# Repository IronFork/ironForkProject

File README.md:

# ironForkProject
 robotic arm helping people with disabilities to eat
 
 https://ironfork.fr

READ ME

I - INTRODUCTION

  a) Présentation
  
  b) Objectifs du projet
  
II - MONTER LE ROBOT

  a) Imprimer les pièces en 3D
  
  b) Se procurer les moteurs
  
  c) Se procurer les composants annexes 
  
III - FAIRE FONCTIONNER LE ROBOT

IV - EXPLICATION DU CODE SOURCE

  a) La partie mécanique 
  
  b) La partie programmation
  
V - PISTES D'AMÉLIORATION

I - INTRODUCTION 

a) Présentation : 
Projet mené par un groupe de 12 étudiants en partenariat avec l'IEM "Christian Dabbadie" dans le cadre de leurs études à Centrale Lille. 

b) Objectifs du projet : 
Concevoir un bras robotique permettant aux personnes en situation de handicap d'avoir une plus grande autonomie lors de leurs repas. 
Projet en open source avec une licence GPL. 
L'un des objectifs du projet est de rendre le bras imprimable en 3D facilement dans un fablab.

I - MONTER LE ROBOT 

Vous aurez besoin d'une imprimante 3D et de ... bobines de PLA. Le reste des composants à commander est indiqué dans les étapes suivantes. Le budget estimé est de 500€ environs. 

a) Imprimer les pièces en 3D : 
Ouvrir le dossier fichiers_stl. Ce dossier contient les fichiers STL de chaque pièce du robot, organisées en sous-ensembles. Un sous-dossier nommé "assemblages" contient les fichiers STL des différents sous-ensembles, et de l'assemblage complet. 

Liste des pièces à imprimer en 3D : 

Pour le socle : 
  - 3 sous-socles différents (c'est le plancher du robot, les 3 sous-socles sont sur le même ficher STL)
  - 1 bol
  - 1 socle (en forme de petite tablette)
  - 1 adaptateur socle-moteur (permet de fixer le moteur sous le socle)
  - 1 poulie socle (poulie fixée sur l'axe moteur)
  
Pour la Tourelle : 
  - 1 Tourelle (placée en liaison pivot avec le socle, elle soutient le bras)
  - 1 poulie tourelle ( poulie fixée dans l'axe de la tourelle et reliée à la poulie socle par une courroie)
  - 2 adaptateurs tourelle-moteurs (permettent de fixer 2 moteurs sur la tourelle)
  
Pour le bras : 
  - 1 bras Tourelle (c'est le bras relié à la tourelle en pivot)
  - 1 adaptateur bras-moteur (permet de fixer le moteur sur le bras)
  
Pour l'avant-bras : 
  - 1 avant-bras (ressemble au bras-tourelle mais est légèrement différent)
  - 1 adaptateur avant-bras-moteur (permet de fixer le moteur)
  
Pour la pince : 
  - 1 pince 

Pour l'assemblage, référez-vous aux fichiers STL représentant les sous-ensembles du robot. 

b) Se procurer les moteurs : 
Vous aurez besoin de cinq moteurs dynamixel XL430-W250-T.
documentation technique sur github : https://github.com/ROBOTIS-GIT/emanual/blob/master/docs/en/dxl/x/xl430-w250.md

c) Se procurer les composants annexes : 
voir notice. (visserie, fils électriques, rasberry pi, carte de programmation, etc... )

d) Assembler le robot : 
Vous devez vous référer au dossier fichiers_stl pour voir le rôle de chaque composant au sein de l'assemblage complet. 
Référez-vous également au schéma électrique pour les différents branchements. 
Référez-vous à la notice pour vous aider

L'assemblage du robot est maintenant terminé. 

II - FAIRE FONCTIONNER LE ROBOT  

[à compléter, en attendant, cf notice.]

III - EXPLICATION DU CODE SOURCE 

a) La partie mécanique

Le schéma cinématique : 
Nous avons choisi un nombre de 5 pièces d'un point de vue cinématique. Elles sont reliées en série au bâti par cinq liaisons pivot. Une pivot verticale lie le BATI avec la TOURELLE, une pivot horizontale lie la TOURELLE au BRAS, une pivot horizontale lie le BRAS à l'AVANT-BRAS, et une liaison pivot horizontale lie l'AVANT-BRAS à la PINCE. 
Ce choix de 4 pièces et de cinq liaisons pivot nous permet de positionner la PINCE à n'importe quel endroit dans l'espace, et de réaliser un maximum de mouvements en gardant la PINCE à l'horizontal (ce qui permet de déplacer une cuillère sans renverser son contenu). Ce choix de cinématique permet des mouvements fluides et précis. Référez-vous au fichier STL de l'assemblage complet pour vous représenter l'architecture du robot. 

La tourelle : 
La tourelle est au bâti par une liason pivot verticale. Cette liaison permet au robot de tourner sur lui même et de déplacer la cuillère de manière grossière latéralement de gauche à droite. 
Cette liasion qui est la première est la seule à supporter toute la structure du robot, et subit donc beaucoup d'efforts. Il y a également beaucoup de forttements, de par l'appui de la tourelle sur le bâti. Nous avons choisi d'utiliser un coussinet à collerette entre le bati et la tourelle pour minimiser les frottements. La liasion est motorisée par un servomoteur Dynamixel positionné à quelques centimètres de la liaison, et relié par une liaison poulie-couroie. Cela permet de résoudre le problème de coaxialité du moteur avec la liasion, et d'écentuels efforts supportés par l'axe du moteur.

La tourelle et le bras : 
La tourelle et le bras sont reliés par une liaison pivot horizontale. Cette liaison contribue grandement au mouvement d'avant en arrière de la cuillère. 
Encore une fois, cette liasion supporte une bonne partie de la structure du robot, surtout quand celui-ci est étendu. Dans ce cas là, le couple dans l'axe de la liaison est particulièrement élevé. C'est pourquoi nous avons choisi de placer non pas un, mais deux servomoteurs Dynamixel en parallèle de manière à pouvoir axionner cette liasion avec une puissance suffisante. Deux adaptateurs sont vissés au bâti avec des vis à bois permettent de fixer les servomoteurs. 

Le bras et l'avant-bras : 
Le bras est relié à l'avant-bras par une liasion pivot motorisée par un servomoteur Dynamixel. Cette laison contribue grandement au mouvement vertical de bas en haut de la cuillère. Un adaptateur vissé au bras par des vis à bois permet de fixer le moteur. 

L'avant-bras et la pince : 
L'avant-bras et la pince sont reliés entre eux par une liaison pivot motorisée par un servomoteur Dynamixel. Cette liaison permet d'effectuer un mouvement vertical de précison, à la manière d'un poignet. Un adaptateur vissé à l'avant-bras permet de fixer le moteur. 

La pince : 
La pince présente une fente ainsi qu'un trou. Ce trou permet d'y placer un insert de filletage, et la fente permet d'y glisser un manche de cuillère. Ainsi, avec une vis de pression, la cuillère peut être bloquée dans la fente. L'avantage de ce système est qu'il permet l'utilisation d'une cuillère quelconque. 

Le bol : 
Un bol imprimé en 3D est fixé sur le support. ce bol a une forme particulière qui permet à la nourriture d'être centrée dans la zone de pelletage. De plus, le rebord avancé peu haut et le rebord éloigné élevé permettent une introduction de la cuillère aisée, et un raclage facilité. L'avantage de ce système est qu'il permet de n'avoir qu'un seul et unique geste de peletage pour le robot. L'inconvénient est le côté sanitaire : il faut imprimer le bol en PET, et les stries de l'impression 3D peuvent occasionner des copeaux de plastiques dans la nourriture lors du raclage. 

b) La partie programmation

Le choix des composants

La trajectoire choisie 

Explication des fichiers 

IV - PISTES D'AMELIORATION

- sécurité, détection d'erreur informatique
- tests en conditions réeelles (personne en situation de handicap)
- améliorer le système de fixation de la cuillère 
- réduire le volume
- trouver des composants moins cher
- reconnaissance faciale
- ...

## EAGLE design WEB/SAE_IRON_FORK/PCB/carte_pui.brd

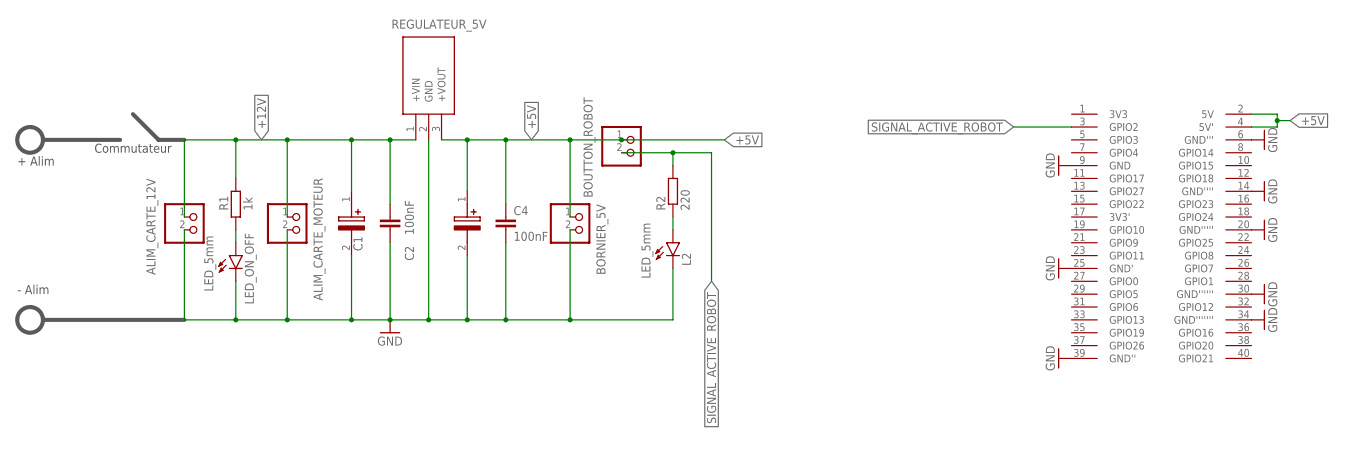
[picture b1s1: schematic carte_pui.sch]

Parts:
ALIM_CARTE_12V: BORNIER_2_ROND_LARGE
ALIM_CARTE_MOTEUR: BORNIER_2_ROND_LARGE
BORNIER_5V: BORNIER_2_ROND_LARGE
BOUTTON_ROBOT: BORNIER_2_ROND_LARGE
C1, C3: 10uF; CAPPRD350W65D800H1300
C2, C4: 100nF; C050-030X040
L2: LED_5mm; LED5MM
LED_ON_OFF: LED_5mm; LED5MM
R1: 1k; 0207/7-90
R2: 220; 0207/7-90
REGULATEUR_5V: TSR_2-2450; TSR-2
U$1: PI4

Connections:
+5V: BORNIER_5V.1, BOUTTON_ROBOT.1, C3.1 (+), C4.1, REGULATEUR_5V.3 (+VOUT), U$1.2 (5V), U$1.4 (5V')
+12V: ALIM_CARTE_12V.1, ALIM_CARTE_MOTEUR.1, C1.1 (+), C2.1, R1.2, REGULATEUR_5V.1 (+VIN)
GND: ALIM_CARTE_12V.2, ALIM_CARTE_MOTEUR.2, BORNIER_5V.2, C1.2 (-), C2.2, C3.2 (-), C4.2, L2.K (C), LED_ON_OFF.K (C), REGULATEUR_5V.2 (GND), U$1.6 (GND'''), U$1.9 (GND), U$1.14 (GND''''), U$1.20 (GND'''''), U$1.25 (GND'), U$1.30 (GND''''''), U$1.34 (GND'''''''), U$1.39 (GND'')
unnamed: LED_ON_OFF.A, R1.1
unnamed: L2.A, R2.1
SIGNAL_ACTIVE_ROBOT: BOUTTON_ROBOT.2, R2.2, U$1.3 (GPIO2)

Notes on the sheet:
Commutateur
+ Alim
- Alim

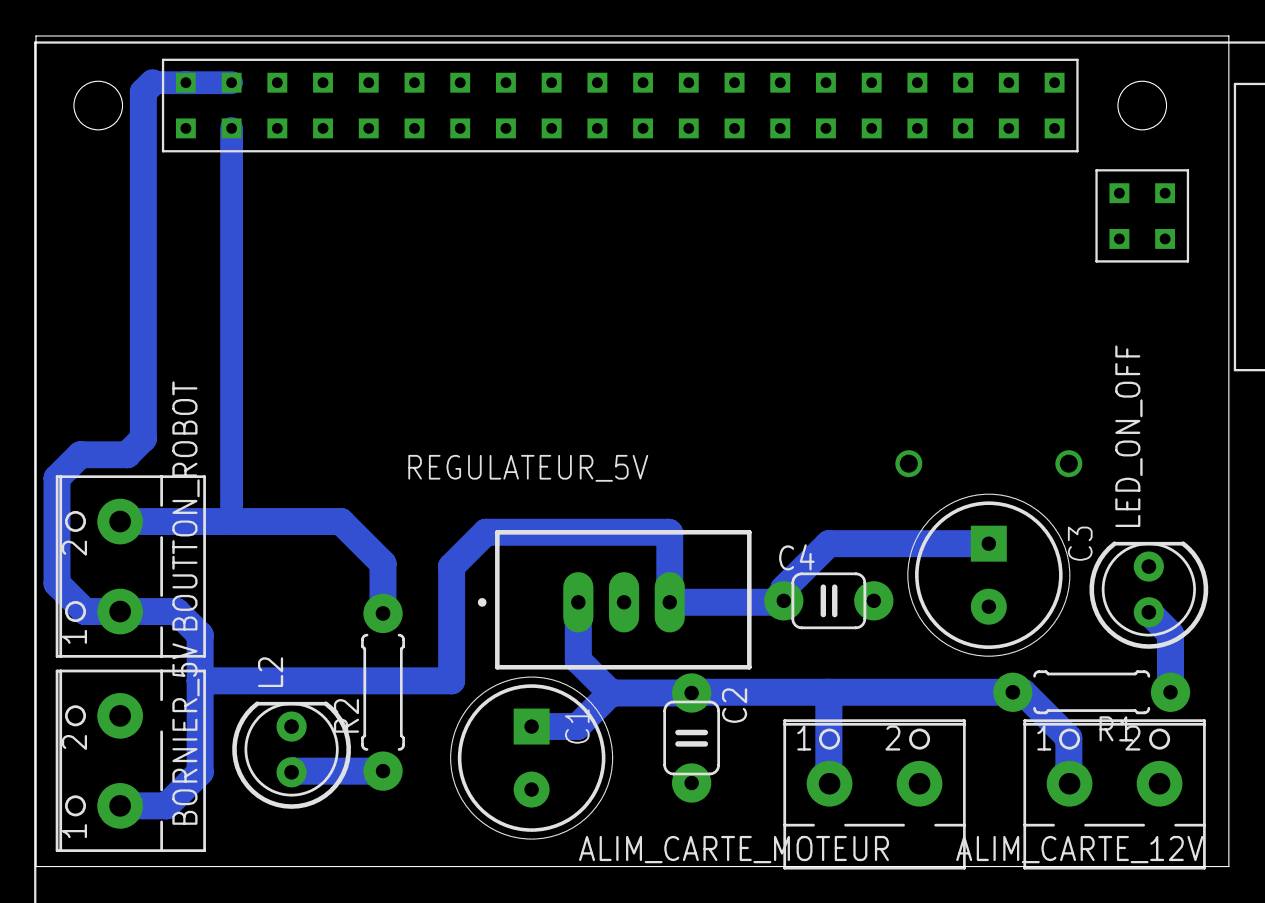
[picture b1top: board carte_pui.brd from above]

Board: 2 copper layers, 66.3 x 46.1 mm, 14 parts (0 on the bottom side), 6 nets.

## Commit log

2021-01-13 CAD files
2021-01-13 path files code
2021-01-13 GPL license
2021-01-13 stp files for arm
2021-01-16 Create documents techniques moteurs
2021-01-28 Create composants_annexes
2021-02-01 Create Assemblages
2025-03-14 supp_web
